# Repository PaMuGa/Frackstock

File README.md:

# Frackstock

LED-Stock der ET15ab und ET14t für die Frackwocke 2018.

## Infos
* LED-Stripes: 2 * 1m (zweiseitig), 60 LEDs/m, WS2812b
* LiIon - Akku
* Steuerung über BLE Uart GATT (Android APP)
* Accelerometer und Gyro-Sensor im Knauf
* NFC für Wakeup und Pairing

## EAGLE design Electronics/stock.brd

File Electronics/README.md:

# Elektronik

Schaltplan und Board.

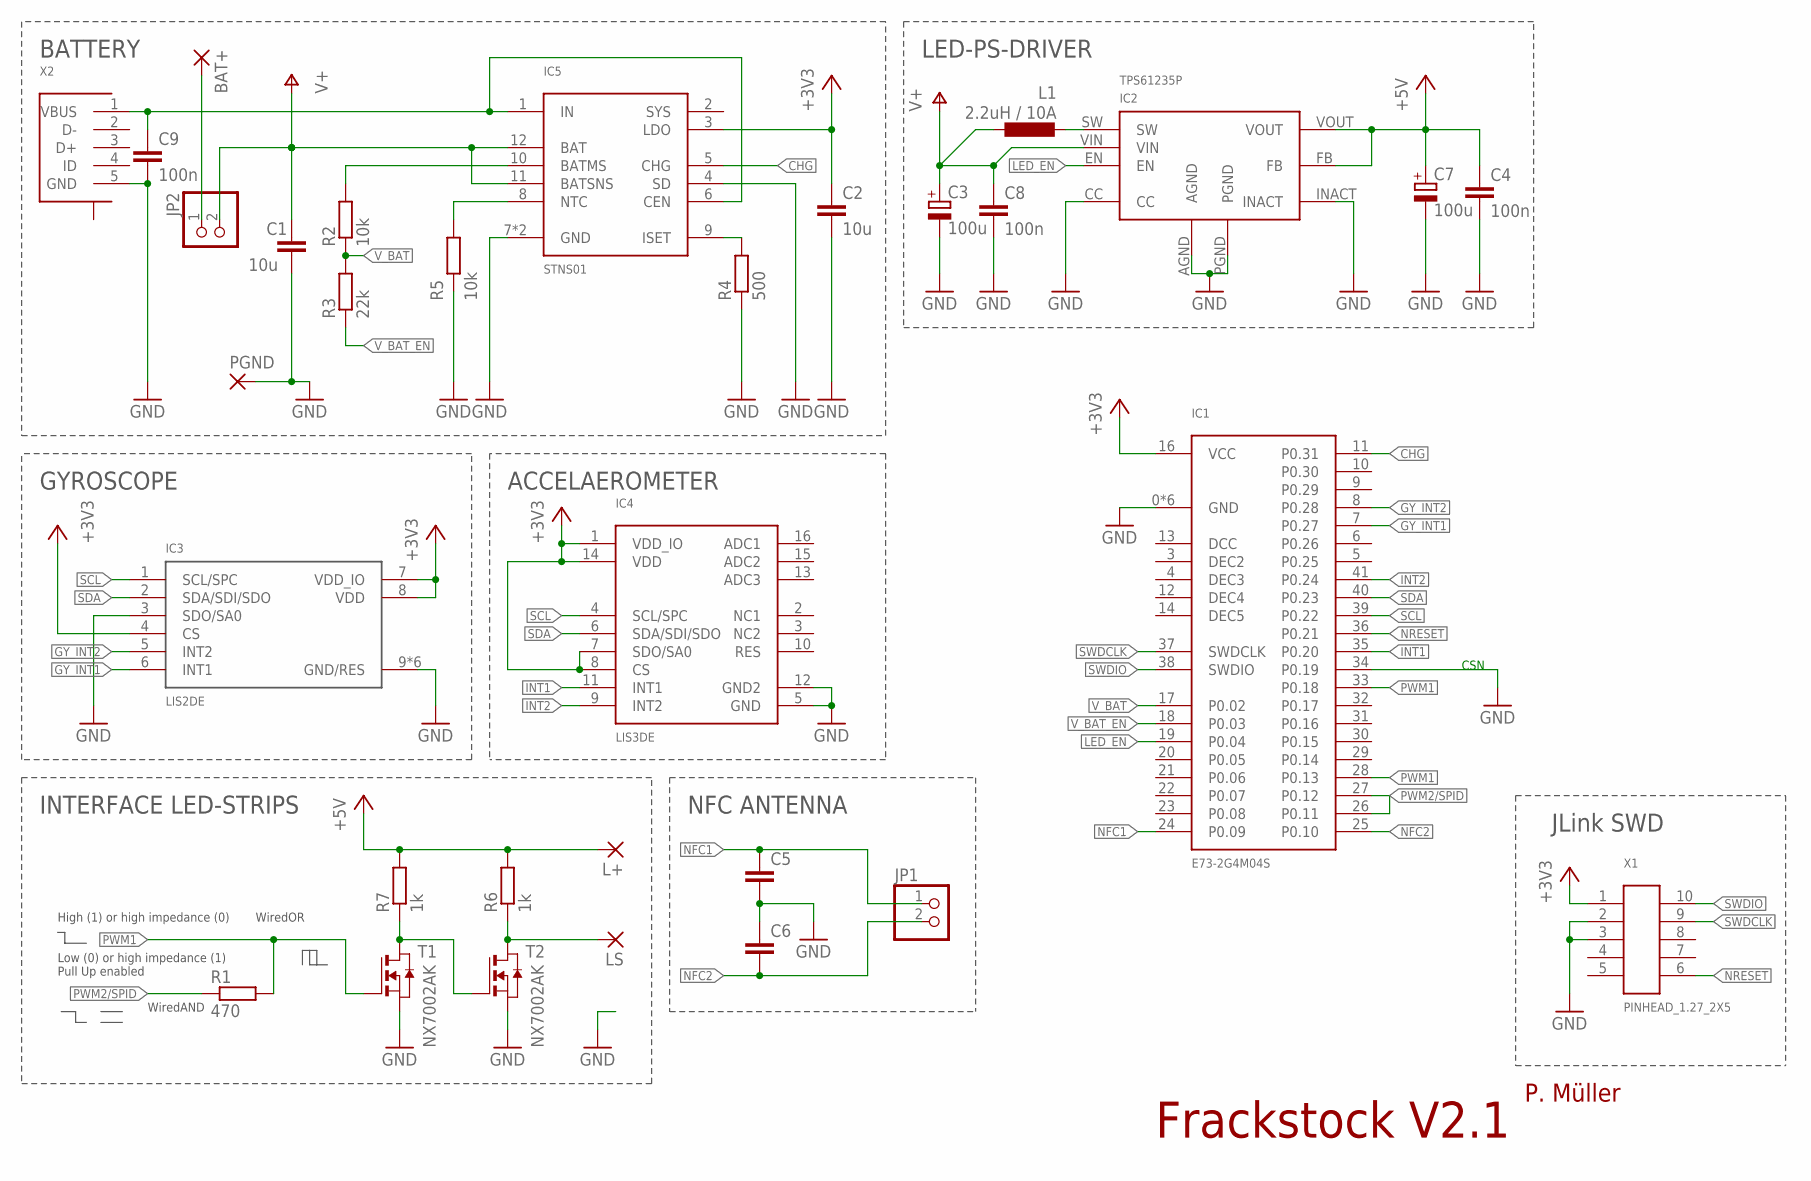
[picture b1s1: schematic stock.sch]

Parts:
BAT+: SMD2; SMD1,27-2,54
C1, C2: 10u; C0805
C3, C7: 100u; SMC_D
C4, C8, C9: 100n; C0805
C5, C6: C-EUC0805; C0805
IC1: E73-2G4M04S
IC2: TPS61235P; TPS6823
IC3: LIS2DE; LGA-14
IC4: LIS3DE; LGA-16
IC5: STNS01; DFN12
JP1, JP2: PINHD-1X2; 1X02
L1: 2.2uH / 10A; L5650M
L+: SMD2; SMD1,27-2,54
LS: SMD2; SMD1,27-2,54
PGND: SMD5; SMD2,54-5,08
R1: 470; R0603
R2, R5: 10k; R0603
R3: 22k; R0603
R4: 500; R0603
R6, R7: 1k; R0603
T1, T2: NX7002AK; SOT-23
X1: PINHEAD_1.27_2X5; PINHEAD_2X5
X2: USB_MICRO_SENKRECHT; USB_MOLEX_SENKRECHT

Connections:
+3V3: C2.1, IC1.16 (VCC), IC3.4 (CS), IC3.7 (VDD_IO), IC3.8 (VDD), IC4.1 (VDD_IO), IC4.7 (SDO/SA0), IC4.8 (CS), IC4.14 (VDD), IC5.3 (LDO), X1.1
+5V: C4.1, C7.+, IC2.FB, IC2.VOUT, L+.1, R6.2, R7.2
CEN: C9.1, IC5.1 (IN), IC5.6 (CEN), X2.1 (VBUS)
CHG: IC1.11 (P0.31), IC5.5 (CHG)
GND: C1.2, C2.2, C3.-, C4.2, C5.2, C6.1, C7.-, C8.2, C9.2, IC1.0 (GND), IC1.1 (GND), IC1.2 (GND), IC1.15 (GND), IC1.34 (P0.19), IC1.42 (GND), IC1.43 (GND), IC2.AGND, IC2.CC, IC2.INACT, IC2.PGND, IC3.3 (SDO/SA0), IC3.9 (GND/RES), IC3.10 (GND/RES), IC3.11 (GND/RES), IC3.12 (GND/RES), IC3.13 (GND/RES), IC3.14 (GND/RES), IC4.5 (GND), IC4.12 (GND2), IC5.4 (SD), IC5.7 (GND), IC5.EXP (GND), PGND.1, R4.1, R5.1, T1.2 (S), T2.2 (S), X1.2, X1.3, X2.5 (GND)
GY_INT1: IC1.7 (P0.27), IC3.6 (INT1)
GY_INT2: IC1.8 (P0.28), IC3.5 (INT2)
INT1: IC1.35 (P0.20), IC4.11 (INT1)
INT2: IC1.41 (P0.24), IC4.9 (INT2)
LED_EN: IC1.19 (P0.04), IC2.EN
unnamed: IC2.SW, L1.2
unnamed: R7.1, T1.1 (D), T2.3 (G)
unnamed: LS.1, R6.1, T2.1 (D)
unnamed: BAT+.1, JP2.1
unnamed: IC5.9 (ISET), R4.2
unnamed: IC5.8 (NTC), R5.2
unnamed: IC5.10 (BATMS), R2.2
NFC1: C5.1, IC1.24 (P0.09), JP1.1
NFC2: C6.2, IC1.25 (P0.10), JP1.2
NRESET: IC1.36 (P0.21), X1.6
PWM1: IC1.28 (P0.13), IC1.33 (P0.18), R1.2, T1.3 (G)
PWM2/SPID: IC1.26 (P0.11), IC1.27 (P0.12), R1.1
SCL: IC1.39 (P0.22), IC3.1 (SCL/SPC), IC4.4 (SCL/SPC)
SDA: IC1.40 (P0.23), IC3.2 (SDA/SDI/SDO), IC4.6 (SDA/SDI/SDO)
SWDCLK: IC1.37 (SWDCLK), X1.9
SWDIO: IC1.38 (SWDIO), X1.10
V+: C1.1, C3.+, C8.1, IC2.VIN, IC5.11 (BATSNS), IC5.12 (BAT), JP2.2, L1.1
V_BAT: IC1.17 (P0.02), R2.1, R3.2
V_BAT_EN: IC1.18 (P0.03), R3.1

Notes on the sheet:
WiredOR
WiredAND
High (1) or high impedance (0)
Low (0) or high impedance (1) Pull Up enabled
BATTERY
LED-PS-DRIVER
INTERFACE LED-STRIPS
NFC ANTENNA
ACCELAEROMETER
Frackstock V2.1
P. Müller
CSN
GYROSCOPE
JLink SWD

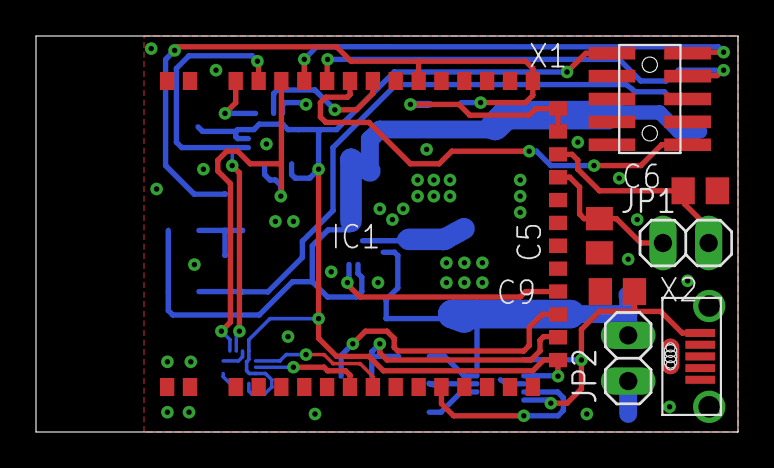
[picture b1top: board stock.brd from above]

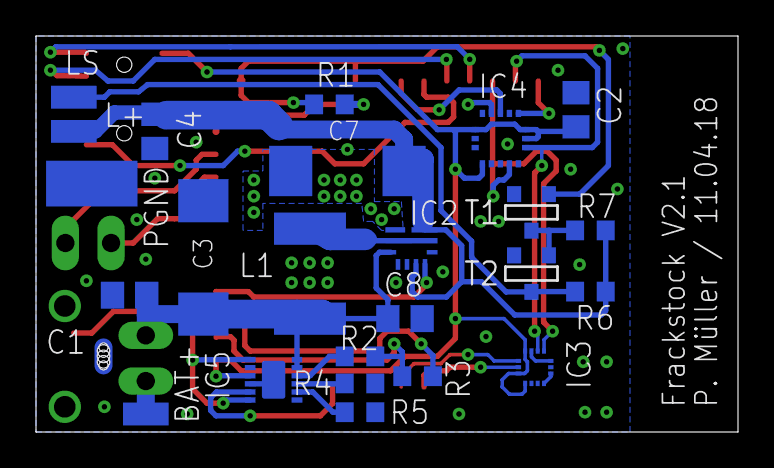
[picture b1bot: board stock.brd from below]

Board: 2 copper layers, 39.0 x 22.0 mm, 32 parts (24 on the bottom side), 29 nets.

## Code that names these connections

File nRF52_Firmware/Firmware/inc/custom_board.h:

/*
* Copyright (c) 2018 Pascal Müller
* 
* Permission is hereby granted, free of charge, to any person obtaining a copy
* of this software and associated documentation files (the "Software"), to deal
* in the Software without restriction, including without limitation the rights
* to use, copy, modify, merge, publish, distribute, sublicense, and/or sell
* copies of the Software, and to permit persons to whom the Software is
* furnished to do so, subject to the following conditions:
*
* The above copyright notice and this permission notice shall be included in
* all copies or substantial portions of the Software.
*
* THE SOFTWARE IS PROVIDED "AS IS", WITHOUT WARRANTY OF ANY KIND, EXPRESS
* OR IMPLIED, INCLUDING BUT NOT LIMITED TO THE WARRANTIES OF 
* MERCHANTABILITY, FITNESS FOR A PARTICULAR PURPOSE AND NONINFRINGEMENT.
* IN NO EVENT SHALL THE AUTHORS OR COPYRIGHT HOLDERS BE LIABLE FOR ANY CLAIM,
* DAMAGES OR OTHER LIABILITY, WHETHER IN AN ACTION OF CONTRACT, TORT OR
* OTHERWISE, ARISING FROM, OUT OF OR IN CONNECTION WITH THE SOFTWARE OR THE
* USE OR OTHER DEALINGS IN THE SOFTWARE.
*/

// PIN Definitions

#define PIN_V_BAT 		2	// Battery voltage after resistance divisor
#define PIN_V_BAT_EN	3	// Pin to enable battery voltage measurement
#define PIN_LED_EN 		4	// Pin to enable boost converter for led voltage
#define PIN_SPI_SPID 	11
#define PIN_PWM2 		12
#define PIN_PWM1 		13
#define PIN_SCL 		22	// I2C SCL signal for sensors
#define PIN_SDA 		23	// I2C SDA signal for sensors
#define PIN_INT1 		20	// Interrupt pin 1 for acc sensor
#define PIN_INT2 		24	// Interrupt pin 2 for acc sensor
#define PIN_SPI_SCK 	18
#define PIN_SPI_CSN 	17
#define PIN_CHG 		31	// Battery charging indication pin

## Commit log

2018-04-18 Verzeichnisstruktur erstellt.
2018-04-18 Initial Android App added
2018-04-19 ConnectActivity: Implemented Searching for Frackstock with High RSSI value, ready for connecting.
2018-04-21 ConnectActivity: Auto connecting implemented. Button for communication testing inserted.
2018-04-23 Schematics and Board added
2018-04-23 3D printing components added
2018-04-23 Firmware added to GitHub
2018-04-25 LIS3DE configuration and readout implemented.
2018-04-25 LIS3DE automated data readout after interrupt.
2018-04-25 Accelerometer data filtering and sending over BLE implemented.
2018-04-26 Bill of material with actual prices updated.
2018-04-26 Launcher icon added.
2018-05-02 Update issue templates
2018-05-07 Patterncontrol added, some improvements and bug fixes
2018-05-08 Changes for compiler optimizations L3
2018-05-10 Improved battery charge measurement, some patterns added.
2018-05-10 Battery charging value corrected after measuring.
2018-05-11 Improved patterncontrol, 32bit control state for more information. Added constant color pattern.
2018-05-13 actual running version, patters not tested. Purple rain is working.
2018-05-14 Improved led driver. Used I2S and DMA. Removed ugly interrupt artifacts.
2018-05-14 Not changing to slave mode after BLE disconnect. Dark blue is "active without Master" signal after startup.
2018-05-14 Changes on battery charging, filter and calculation. Updated project settings.
2018-05-16 Filter improved for stable battery charge measurement.
2018-05-16 Added some control informations about master and slave mode for the android application.
2018-05-16 Better Bluetooth functionality.
2018-05-17 improved application information for smartphone
2018-05-17 merged with led_patterns branch
2018-05-17 Added releases
2018-05-19 Bugfix on battery and charge measurement.
2018-05-19 Extended information for the android application
2018-05-19 Improved log output if the stick isn't beeing charged.
2018-05-19 Improved enable / disable of leds, removes wrong colors in charging state
2018-05-19 Log output only if "DEBUG" is defined. Removed "DEBUG" in project settings.
2018-05-19 Increased update frequency of application data for the smartphone
2018-05-19 Bugfix in color mode
2018-05-19 Improved application
2018-05-20 Different changes in NFC, patterncontrol and licensing
2018-05-20 Frackwoche 2018 App release
2018-05-20 Created new branch with new patterns
2018-05-20 Added new Patterns Colorflash and added random generator for shift pattern
2018-05-21 Merged new patterns Shift and Colorflash
2018-05-21 New patterns in android app implemented (Shift and Colorflash)
2018-05-22 Main master preferring if multiple masters are available
2018-05-22 Frackwoche release
2018-05-22 Reduced advertising interval
2018-06-27 Changed target sdk version to 25 for Android 8. Issue #11. Untested
